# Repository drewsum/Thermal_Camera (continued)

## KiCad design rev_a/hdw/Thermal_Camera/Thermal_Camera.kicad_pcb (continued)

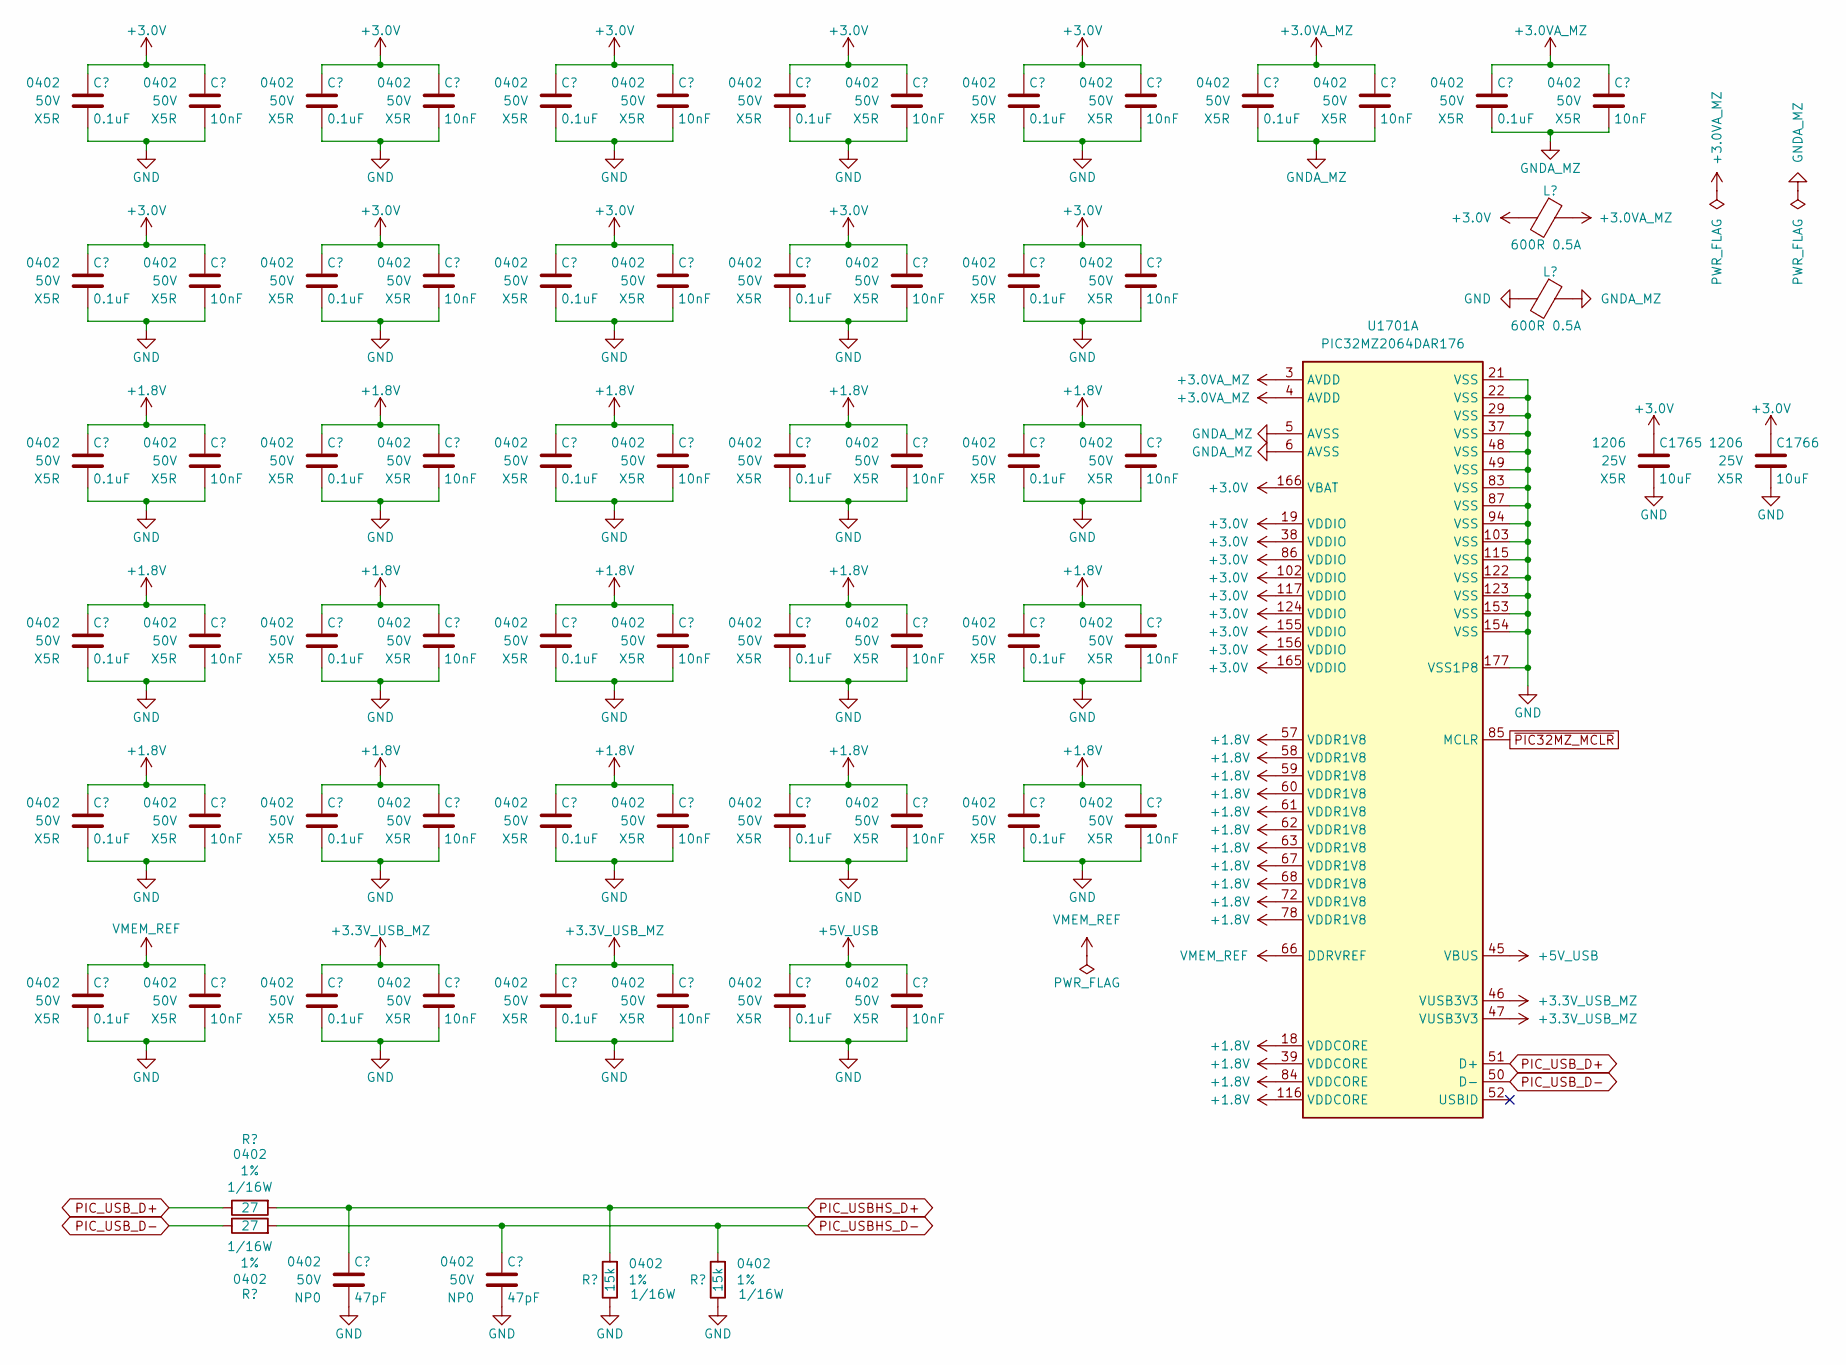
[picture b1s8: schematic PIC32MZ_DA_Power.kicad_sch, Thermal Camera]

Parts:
C1701, C1702, C1703, C1704, C1705, C1706, C1713, C1714, C1715, C1716, C1717, C1718, C1727, C1728, C1729, C1730, C1731, C1732, C1739, C1740, C1741, C1742, C1743, C1744, C1751, C1752, C1753, C1754, C1755, C1761, C1763: 0.1uF; C_0402; Voltage 50V; Digi-Key PN 490-10697-1-ND
C1707, C1708, C1709, C1710, C1711, C1712, C1720, C1721, C1722, C1723, C1724, C1725, C1733, C1734, C1735, C1736, C1737, C1738, C1745, C1746, C1747, C1748, C1749, C1750, C1756, C1757, C1758, C1759, C1760, C1762, C1764: 10nF; C_0402; Voltage 50V; Digi-Key PN 445-12201-1-ND
C1719, C1726: 47pF; C_0402; Voltage 50V; Digi-Key PN 490-5942-1-ND
C1765, C1766: 10uF; C_1206; Voltage 25V; Digi-Key PN 399-8153-1-ND
L1701, L1702: 600R 0.5A; L_0402
R1701, R1702: 27; R_0402; Tolerance 1%; Digi-Key PN RMCF0402FT27R0CT-ND
R1703, R1704: 15k; R_0402; Tolerance 1%; Digi-Key PN RMCF0402FT15K0CT-ND
U1701: PIC32MZ2064DAR176; LQFP-176_20x20mm_P0.4mm_7p9x7p9mm_EP; Digi-Key PN PIC32MZ2064DAR176-I/2J-ND

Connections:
+1.8V: C1703.1, C1704.1, C1705.1, C1709.1, C1710.1, C1711.1, C1715.1, C1716.1, C1717.1, C1722.1, C1723.1, C1724.1, C1729.1, C1730.1, C1731.1, C1735.1, C1736.1, C1737.1, C1741.1, C1742.1, C1743.1, C1747.1, C1748.1, C1749.1, C1753.1, C1754.1, C1755.1, C1758.1, C1759.1, C1760.1, U1701.18 (VDDCORE), U1701.39 (VDDCORE), U1701.57 (VDDR1V8), U1701.58 (VDDR1V8), U1701.59 (VDDR1V8), U1701.60 (VDDR1V8), U1701.61 (VDDR1V8), U1701.62 (VDDR1V8), U1701.63 (VDDR1V8), U1701.67 (VDDR1V8), U1701.68 (VDDR1V8), U1701.72 (VDDR1V8), U1701.78 (VDDR1V8), U1701.84 (VDDCORE), U1701.116 (VDDCORE); also elsewhere on the board
+3.0V: C1701.1, C1702.1, C1707.1, C1708.1, C1713.1, C1714.1, C1720.1, C1721.1, C1727.1, C1728.1, C1733.1, C1734.1, C1739.1, C1740.1, C1745.1, C1746.1, C1751.1, C1752.1, C1756.1, C1757.1, C1765.1, C1766.1, L1701.2, U1701.19 (VDDIO), U1701.38 (VDDIO), U1701.86 (VDDIO), U1701.102 (VDDIO), U1701.117 (VDDIO), U1701.124 (VDDIO), U1701.155 (VDDIO), U1701.156 (VDDIO), U1701.165 (VDDIO), U1701.166 (VBAT); also elsewhere on the board
+3.0VA_MZ: C1761.1, C1762.1, C1763.1, C1764.1, L1701.1, U1701.3 (AVDD), U1701.4 (AVDD)
+3.3V_USB_MZ: C1718.1, C1725.1, C1732.1, C1738.1, U1701.46 (VUSB3V3), U1701.47 (VUSB3V3)
+5V_USB: C1744.1, C1750.1, U1701.45 (VBUS); also elsewhere on the board
GND: C1701.2, C1702.2, C1703.2, C1704.2, C1705.2, C1706.2, C1707.2, C1708.2, C1709.2, C1710.2, C1711.2, C1712.2, C1713.2, C1714.2, C1715.2, C1716.2, C1717.2, C1718.2, C1719.2, C1720.2, C1721.2, C1722.2, C1723.2, C1724.2, C1725.2, C1726.2, C1727.2, C1728.2, C1729.2, C1730.2, C1731.2, C1732.2, C1733.2, C1734.2, C1735.2, C1736.2, C1737.2, C1738.2, C1739.2, C1740.2, C1741.2, C1742.2, C1743.2, C1744.2, C1745.2, C1746.2, C1747.2, C1748.2, C1749.2, C1750.2, C1751.2, C1752.2, C1753.2, C1754.2, C1755.2, C1756.2, C1757.2, C1758.2, C1759.2, C1760.2, C1765.2, C1766.2, L1702.2, R1703.2, R1704.2, U1701.21 (VSS), U1701.22 (VSS), U1701.29 (VSS), U1701.37 (VSS), U1701.48 (VSS), U1701.49 (VSS), U1701.83 (VSS), U1701.87 (VSS), U1701.94 (VSS), U1701.103 (VSS), U1701.115 (VSS), U1701.122 (VSS), U1701.123 (VSS), U1701.153 (VSS), U1701.154 (VSS), U1701.177 (VSS1P8); also elsewhere on the board
GNDA_MZ: C1761.2, C1762.2, C1763.2, C1764.2, L1702.1, U1701.5 (AVSS), U1701.6 (AVSS)
PIC_USBHS_D+: C1719.1, R1701.1, R1703.1; also elsewhere on the board
PIC_USBHS_D-: C1726.1, R1702.1, R1704.1; also elsewhere on the board
PIC_USB_D+: R1701.2, U1701.51 (D+)
PIC_USB_D-: R1702.2, U1701.50 (D-)
VMEM_REF: C1706.1, C1712.1, U1701.66 (DDRVREF)
~PIC32MZ_MCLR: U1701.85 (MCLR); also elsewhere on the board

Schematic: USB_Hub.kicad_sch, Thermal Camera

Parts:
C2501, C2502, C2503, C2504, C2506, C2507, C2509: 0.1uF; C_0402; Voltage 50V; Digi-Key PN 490-10697-1-ND
C2505, C2508: 10uF; C_0402; Voltage 10V; Digi-Key PN 490-GRM155R61A106ME11DCT-ND
L2501: 600R 0.5A; L_0402
R2501: 10; R_0402; Tolerance 1%; Digi-Key PN RMCF0402FT10R0CT-ND
R2502, R2503, R2504, R2505, R2506, R2507: 10k; R_0402; Tolerance 1%; Digi-Key PN RMCF0402FT10K0CT-ND
SW2501: RESET; SW_PUSH_6mm
U2501, U2503: 74LVC1G97; SOT-363_SC-70-6; Digi-Key PN 296-15582-1-ND
U2502: TPS3808G33; SOT-23-6; Digi-Key PN 296-17195-1-ND
U2504: TUSB2046BIRHBT; VQFN-32-1EP_5x5mm_P0.5mm_EP3.5x3.5mm; Digi-Key PN 296-27130-1-ND
X2501: ASE-48.000MHz; Oscillator_SMD_Abracon_ASE-4Pin_3.2x2.5mm; Digi-Key PN 535-ASE-48.000MHZ-L-C-TCT-ND

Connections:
+3.3V_USB: C2502.1, C2503.1, C2506.1, C2507.1, C2508.1, C2509.1, L2501.2, R2504.1, R2507.1, U2501.5 (VCC), U2502.5 (SENSE), U2502.6 (VDD), U2503.5 (VCC), U2504.3 (VCC), U2504.8 (BUSPWR), U2504.25 (VCC), U2504.26 (~EXTMEM), U2504.30 (XTAL1), U2504.31 (TSTMODE); also elsewhere on the board
BRIDGE_USB_D+: U2504.12 (DP1); also elsewhere on the board
BRIDGE_USB_D-: U2504.11 (DM1); also elsewhere on the board
GND: C2501.2, C2502.2, C2503.2, C2504.2, C2505.2, C2506.2, C2507.2, C2508.2, C2509.2, R2502.2, R2503.2, R2505.2, R2506.2, SW2501.1, U2501.2 (GND), U2501.3 (GND), U2501.6 (GND), U2502.2 (GND), U2503.2 (GND), U2503.3 (GND), U2503.6 (GND), U2504.6 (EEDATA/GANGED), U2504.7 (GND), U2504.28 (GND), U2504.33 (EP), X2501.2 (GND); also elsewhere on the board
HUB_48MHCLK: R2501.2, U2504.27 (TSTPLL/48MCLK)
HUB_CLK_EN: R2503.1, U2501.4, X2501.1 (EN)
HUB_SUSPND: R2505.1, U2503.4; also elsewhere on the board
unnamed: C2501.1, U2502.4 (CT)
unnamed: SW2501.2, U2502.3 (~MR)
unnamed: R2506.1, U2503.1, U2504.32 (SUSPND)
unnamed: R2507.2, U2504.10 (~OVRCUR1), U2504.14 (~OVRCUR2), U2504.18 (~OVRCUR3), U2504.22 (~OVRCUR4)
unnamed: R2501.1, R2502.1, X2501.3 (OUT)
unnamed: C2504.1, C2505.1, L2501.1, X2501.4 (Vdd)
PIC_USBHS_D+: U2504.16 (DP2); also elsewhere on the board
PIC_USBHS_D-: U2504.15 (DM2); also elsewhere on the board
POS3P3_USB_PGOOD: U2501.1; also elsewhere on the board
UFP_USB_D+: U2504.1 (DP0); also elsewhere on the board
UFP_USB_D-: U2504.2 (DM0); also elsewhere on the board
~HUB_RESET: R2504.2, U2502.1 (~RESET), U2504.4 (~RESET)

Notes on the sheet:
Generally, a reset with a pulse width between 100 μs and 1 ms is recommended after 3.3-V VCC reaches its 90%. Clock signal has to be active during the last 60 μs of the reset window.
Strap PLL for 48MHz clocking option See Figure 7 of D/S

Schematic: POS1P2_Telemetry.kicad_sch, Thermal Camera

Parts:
C1101, C1102, C1103: 0.1uF; C_0402; Voltage 50V; Digi-Key PN 490-10697-1-ND
DOC1101: 0x74
DOC1102: 0x1C
U1101: INA231A; Texas_DSBGA-12_1.65x1.39mm_Layout3x4_P0.4mm; Digi-Key PN 296-41263-1-ND
U1102: MCP9804; DFN-8-1EP_3x2mm_P0.5mm_EP1.3x1.5mm; Digi-Key PN MCP9804T-E/MCCT-ND

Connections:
+1.2V: U1101.D1 (BUS); also elsewhere on the board
+3.0V: C1102.1, C1103.1, U1101.B1 (VS), U1101.C3 (A1), U1102.5 (A2), U1102.8 (V_{DD}); also elsewhere on the board
GND: C1102.2, C1103.2, U1101.B3 (A0), U1101.C1 (GND), U1102.4 (GND), U1102.6 (A1), U1102.7 (A0), U1102.9 (EP/GND); also elsewhere on the board
I2C_SCL: U1101.A1 (SCL), U1102.2 (SCL); also elsewhere on the board
I2C_SDA: U1101.A2 (SDA), U1102.1 (SDA); also elsewhere on the board
POS1P2_SNS+: C1101.1, U1101.D3 (IN+)
POS1P2_SNS-: C1101.2, U1101.D2 (IN-)

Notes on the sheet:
Max Current = 3.1A RSHUNT = 0.02 Ohm CLSB = 9.46045E-05A CAL Register = 0x0A92

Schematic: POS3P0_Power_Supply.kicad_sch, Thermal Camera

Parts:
C401, C406: 0.1uF; C_0402; Voltage 50V; Digi-Key PN 490-10697-1-ND
C402, C404, C407, C408: 10uF; C_1206; Voltage 25V; Digi-Key PN 399-8153-1-ND
C403: 10uF; C_0402; Voltage 10V; Digi-Key PN 490-GRM155R61A106ME11DCT-ND
C405: 10nF; C_0402; Voltage 50V; Digi-Key PN 445-12201-1-ND
D401: BAT48JFILM; D_SOD-323; Digi-Key PN 497-5711-1-ND
L401: 2.2uH; L_Vishay_IHLP-2020; Tolerance 20%; Digi-Key PN 541-1236-1-ND
Q401: BSS214NW; SOT-323_SC-70; Digi-Key PN BSS214NWH6327XTSA1CT-ND
Q402: ZXMS6004FFTA; SOT-23; Digi-Key PN ZXMS6004FFCT-ND
R401, R405, R407: 10; R_0402; Tolerance 1%; Digi-Key PN RMCF0402FT10R0CT-ND
R402, R403, R404: 10k; R_0402; Tolerance 1%; Digi-Key PN RMCF0402FT10K0CT-ND
R406: 0.02; R_0612; Tolerance 1%; Digi-Key PN P16010CT-ND
R408: 3.16k; R_0402; Tolerance 1%; Digi-Key PN RMCF0402FT3K16CT-ND
R409: 1.15k; R_0402; Tolerance 1%; Digi-Key PN RMCF0402FT1K15CT-ND
TP401: TP; Test_Point
U401: 74LVC1G97; SOT-363_SC-70-6; Digi-Key PN 296-15582-1-ND
U402: TPS62130A; QFN-16-1EP_3x3mm_P0.5mm_EP1.75x1.75mm; Digi-Key PN 296-39446-1-ND

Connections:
+3.0V: C401.1, D401.2 (A), Q402.3 (D), R403.1, R406.2, R407.2, R408.1, TP401.1 (TP), U401.5 (VCC), U402.14 (VOS); also elsewhere on the board
GND: C401.2, C402.2, C403.2, C404.2, C405.2, C406.2, C407.2, C408.2, Q401.2 (S), Q402.2 (S), R402.2, R409.2, U401.1 (GND), U401.2 (GND), U402.6 (AGND), U402.7 (FSW), U402.8 (DEF), U402.15 (PGND), U402.16 (PGND), U402.17 (EP); also elsewhere on the board
unnamed: C407.1, C408.1, L401.2, R405.2, R406.1
unnamed: C403.1, D401.1 (K), R404.1
unnamed: L401.1, U402.1 (SW), U402.2 (SW), U402.3 (SW)
unnamed: Q401.3 (D), Q402.1 (G), R404.2
unnamed: R408.2, R409.1, U402.5 (FB)
unnamed: R403.2, U401.6, U402.4 (PG)
unnamed: C405.1, U402.9 (SS/TR)
POS3P0_PGOOD: R402.1, U401.4; also elsewhere on the board
POS3P0_RUN: Q401.1 (G), R401.2, U401.3, U402.13 (EN)
POS3P0_SNS+: R405.1; also elsewhere on the board
POS3P0_SNS-: R407.1; also elsewhere on the board
POS12_PGOOD: R401.1; also elsewhere on the board
VCOM: C402.1, C404.1, C406.1, U402.10 (AVIN), U402.11 (PVIN), U402.12 (PVIN); also elsewhere on the board

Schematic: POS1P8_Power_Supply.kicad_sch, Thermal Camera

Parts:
C601, C606: 0.1uF; C_0402; Voltage 50V; Digi-Key PN 490-10697-1-ND
C602, C604, C607, C608: 10uF; C_1206; Voltage 25V; Digi-Key PN 399-8153-1-ND
C603: 10uF; C_0402; Voltage 10V; Digi-Key PN 490-GRM155R61A106ME11DCT-ND
C605: 10nF; C_0402; Voltage 50V; Digi-Key PN 445-12201-1-ND
D601: BAT48JFILM; D_SOD-323; Digi-Key PN 497-5711-1-ND
L601: 2.2uH; L_Vishay_IHLP-2020; Tolerance 20%; Digi-Key PN 541-1236-1-ND
Q601: BSS214NW; SOT-323_SC-70; Digi-Key PN BSS214NWH6327XTSA1CT-ND
Q602: ZXMS6004FFTA; SOT-23; Digi-Key PN ZXMS6004FFCT-ND
R601, R605, R607: 10; R_0402; Tolerance 1%; Digi-Key PN RMCF0402FT10R0CT-ND
R602, R603, R604: 10k; R_0402; Tolerance 1%; Digi-Key PN RMCF0402FT10K0CT-ND
R606: 0.02; R_0612; Tolerance 1%; Digi-Key PN P16010CT-ND
R608: 1.87k; R_0402; Tolerance 1%; Digi-Key PN RMCF0402FT1K87CT-ND
R609: 1.5k; R_0402; Tolerance 1%; Digi-Key PN RMCF0402FT1K50CT-ND
TP601: TP; Test_Point
U601: 74LVC1G97; SOT-363_SC-70-6; Digi-Key PN 296-15582-1-ND
U602: TPS62130A; QFN-16-1EP_3x3mm_P0.5mm_EP1.75x1.75mm; Digi-Key PN 296-39446-1-ND

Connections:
+1.8V: Q602.3 (D), R606.2, R607.2, R608.1, TP601.1 (TP), U602.14 (VOS); also elsewhere on the board
+3.0V: C601.1, D601.2 (A), R603.1, U601.5 (VCC); also elsewhere on the board
GND: C601.2, C602.2, C603.2, C604.2, C605.2, C606.2, C607.2, C608.2, Q601.2 (S), Q602.2 (S), R602.2, R609.2, U601.1 (GND), U601.2 (GND), U602.6 (AGND), U602.7 (FSW), U602.8 (DEF), U602.15 (PGND), U602.16 (PGND), U602.17 (EP); also elsewhere on the board
unnamed: C607.1, C608.1, L601.2, R605.2, R606.1
unnamed: C603.1, D601.1 (K), R604.1
unnamed: L601.1, U602.1 (SW), U602.2 (SW), U602.3 (SW)
unnamed: Q601.3 (D), Q602.1 (G), R604.2
unnamed: R608.2, R609.1, U602.5 (FB)
unnamed: R603.2, U601.6, U602.4 (PG)
unnamed: C605.1, U602.9 (SS/TR)
POS1P8_PGOOD: R602.1, U601.4; also elsewhere on the board
POS1P8_RUN: Q601.1 (G), R601.2, U601.3, U602.13 (EN)
POS1P8_SNS+: R605.1; also elsewhere on the board
POS1P8_SNS-: R607.1; also elsewhere on the board
POS3P0_PGOOD: R601.1; also elsewhere on the board
VCOM: C602.1, C604.1, C606.1, U602.10 (AVIN), U602.11 (PVIN), U602.12 (PVIN); also elsewhere on the board

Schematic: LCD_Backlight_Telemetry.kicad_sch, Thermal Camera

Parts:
C1301, C1302, C1303: 0.1uF; C_0402; Voltage 50V; Digi-Key PN 490-10697-1-ND
DOC1301: 0x75
DOC1302: 0x1D
U1301: INA231A; Texas_DSBGA-12_1.65x1.39mm_Layout3x4_P0.4mm; Digi-Key PN 296-41263-1-ND
U1302: MCP9804; DFN-8-1EP_3x2mm_P0.5mm_EP1.3x1.5mm; Digi-Key PN MCP9804T-E/MCCT-ND

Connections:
+3.0V: C1302.1, C1303.1, U1301.B1 (VS), U1301.B3 (A0), U1301.C3 (A1), U1302.5 (A2), U1302.7 (A0), U1302.8 (V_{DD}); also elsewhere on the board
BACKLIGHT_ANODE: U1301.D1 (BUS); also elsewhere on the board
GND: C1302.2, C1303.2, U1301.C1 (GND), U1302.4 (GND), U1302.6 (A1), U1302.9 (EP/GND); also elsewhere on the board
I2C_SCL: U1301.A1 (SCL), U1302.2 (SCL); also elsewhere on the board
I2C_SDA: U1301.A2 (SDA), U1302.1 (SDA); also elsewhere on the board
VLED_SNS+: C1301.1, U1301.D3 (IN+); also elsewhere on the board
VLED_SNS-: C1301.2, U1301.D2 (IN-); also elsewhere on the board

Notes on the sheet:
Max Current = 3.1A RSHUNT = 0.02 Ohm CLSB = 9.46045E-05A CAL Register = 0x0A92

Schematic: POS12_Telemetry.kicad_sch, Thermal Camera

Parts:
C301, C302, C303: 0.1uF; C_0402; Voltage 50V; Digi-Key PN 490-10697-1-ND
DOC301: 0x70
DOC302: 0x18
U301: INA231A; Texas_DSBGA-12_1.65x1.39mm_Layout3x4_P0.4mm; Digi-Key PN 296-41263-1-ND
U302: MCP9804; DFN-8-1EP_3x2mm_P0.5mm_EP1.3x1.5mm; Digi-Key PN MCP9804T-E/MCCT-ND

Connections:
+3.0V: C302.1, C303.1, U301.B1 (VS), U302.8 (V_{DD}); also elsewhere on the board
+12V: U301.D1 (BUS); also elsewhere on the board
GND: C302.2, C303.2, U301.B3 (A0), U301.C1 (GND), U301.C3 (A1), U302.4 (GND), U302.5 (A2), U302.6 (A1), U302.7 (A0), U302.9 (EP/GND); also elsewhere on the board
I2C_SCL: U301.A1 (SCL), U302.2 (SCL); also elsewhere on the board
I2C_SDA: U301.A2 (SDA), U302.1 (SDA); also elsewhere on the board
POS12_SNS+: C301.1, U301.D3 (IN+); also elsewhere on the board
POS12_SNS-: C301.2, U301.D2 (IN-); also elsewhere on the board

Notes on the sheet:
Max Current = 3.1A RSHUNT = 0.02 Ohm CLSB = 9.46045E-05A CAL Register = 0x0A92

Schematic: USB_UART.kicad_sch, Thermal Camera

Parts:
C2201, C2202, C2203, C2204, C2207, C2210: 0.1uF; C_0402; Voltage 50V; Digi-Key PN 490-10697-1-ND
C2205, C2206, C2211: 10uF; C_0402; Voltage 10V; Digi-Key PN 490-GRM155R61A106ME11DCT-ND
C2208, C2209: 47pF; C_0402; Voltage 50V; Digi-Key PN 490-5942-1-ND
D2201: Yellow; LED_0402; Digi-Key PN VLMY1500-GS08CT-ND
DOC2201: COM_Port_Settings
R2201: 1k; R_0402; Tolerance 1%; Digi-Key PN RMCF0402FT1K00CT-ND
R2202: 10k; R_0402; Tolerance 1%; Digi-Key PN RMCF0402FT10K0CT-ND
R2203, R2204: 27; R_0402; Tolerance 1%; Digi-Key PN RMCF0402FT27R0CT-ND
R2205, R2206: 15k; R_0402; Tolerance 1%; Digi-Key PN RMCF0402FT15K0CT-ND
U2201: FT234XD; DFN-12-1EP_3x3mm_Pitch0.45mm; Digi-Key PN 768-1178-1-ND
U2202: 74LVC1G97; SOT-363_SC-70-6; Digi-Key PN 296-15582-1-ND
U2203: FXMA108; WQFN-20-1EP_2.5x4.5mm_P0.5mm_EP1x2.9mm; Digi-Key PN FXMA108BQX

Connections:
+3.0V: C2202.1, C2204.1, C2205.1, R2202.1, U2202.1 (VCC), U2202.5 (VCC), U2203.1 (VCCA); also elsewhere on the board
+3.3V_USB: C2201.1, C2210.1, C2211.1, U2201.9 (VCCIO), U2203.20 (VCCB); also elsewhere on the board
+5V_USB: C2203.1, C2206.1, R2201.1, U2201.4 (VCC); also elsewhere on the board
/USB UART/BRIDGE_USB+: R2203.2, U2201.12 (USBDP)
/USB UART/BRIDGE_USB-: R2204.2, U2201.1 (USBDM)
BRIDGE_USB_D+: C2208.1, R2203.1, R2205.1; also elsewhere on the board
BRIDGE_USB_D-: C2209.1, R2204.1, R2206.1; also elsewhere on the board
GND: C2201.2, C2202.2, C2203.2, C2204.2, C2205.2, C2206.2, C2207.2, C2208.2, C2209.2, C2210.2, C2211.2, R2205.2, R2206.2, U2201.5 (GND), U2201.13 (GND), U2202.2 (GND), U2202.3 (GND), U2203.10 (GND); also elsewhere on the board
unnamed: D2201.2 (A), R2201.2
unnamed: C2207.1, U2201.3 (3V3OUT)
unnamed: R2202.2, U2202.4, U2203.11 (~OE)
POS3P0_PGOOD: U2202.6; also elsewhere on the board
POS3P3_USB_PGOOD: U2201.2 (~RESET); also elsewhere on the board
USB_UART_RX: U2203.2 (A0); also elsewhere on the board
USB_UART_RX_BUF: U2201.7 (TXD), U2203.19 (B0)
USB_UART_TX: U2203.3 (A1); also elsewhere on the board
USB_UART_TX_BUF: U2201.10 (RXD), U2203.18 (B1)
~USB_ACTIVE: D2201.1 (K), U2201.6 (CBUS0)
~USB_UART_CTS_BUF: U2201.11 (~CTS), U2203.16 (B3)
~USB_UART_CTS: U2203.5 (A3); also elsewhere on the board
~USB_UART_RTS_BUF: U2201.8 (~RTS), U2203.17 (B2)
~USB_UART_RTS: U2203.4 (A2); also elsewhere on the board

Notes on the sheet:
FXMA108 recommends no pull resistors

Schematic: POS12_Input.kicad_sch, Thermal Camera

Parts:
C201: 10nF; C_0402; Voltage 50V; Digi-Key PN 445-12201-1-ND
C202: 0.1uF; C_0402; Voltage 50V; Digi-Key PN 490-10697-1-ND
C203: 100uF; CP_EIA-7343-43_Kemet-X; Voltage 16V; Tolerance 10%; Digi-Key PN 718-1102-1-ND
D201: 24V; D_SMA; Digi-Key PN SMAJ24CALFCT-ND; not fitted
J201: +12V IN; BARREL_JACK
N201: +12V 1A Power Supply; Digi-Key PN 993-1335-ND
R201: 51.1k; R_0402; Tolerance 1%; Digi-Key PN RMCF0402FT51K1CT-ND
R202, R209: 1.15k; R_0402; Tolerance 1%; Digi-Key PN RMCF0402FT1K15CT-ND
R203, R208: 5.11k; R_0402; Tolerance 1%; Digi-Key PN RMCF0402FT5K11CT-ND
R204, R206, R211: 10k; R_0402; Tolerance 1%; Digi-Key PN RMCF0402FT10K0CT-ND
R205, R210: 10; R_0402; Tolerance 1%; Digi-Key PN RMCF0402FT10R0CT-ND
R207: 0.02; R_0612; Tolerance 1%; Digi-Key PN P16010CT-ND
TP201: TP; PinHeader_1x01_P2.54mm_Horizontal
TP202, TP203: TP; Test_Point
U201: TPS26600RHFT; QFN-24-1EP_4x5mm_Pitch0.5mm; Digi-Key PN 296-45478-1-ND

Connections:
+12V: C203.1, R207.2, R208.1, R210.2, TP203.1 (TP); also elsewhere on the board
+12Vin: C202.1, D201.1 (A1), J201.1, R201.1, R204.1, TP202.1 (TP), U201.8 (IN), U201.9 (IN)
GND: C202.2, C203.2, D201.2 (A2), J201.2, J201.3, R209.2, TP201.1 (TP), U201.17 (GND); also elsewhere on the board
unnamed: R205.2, R207.1, U201.23 (OUT), U201.24 (OUT)
unnamed: R206.1, U201.19 (ILIM)
unnamed: R211.1, U201.18 (IMON)
unnamed: R202.2, R203.1, U201.12 (OVP)
unnamed: C201.2, R203.2, R206.2, R211.2, U201.15 (RTN), U201.25 (RTN_PAD)
unnamed: R201.2, R202.1, U201.10 (UVLO)
unnamed: C201.1, U201.20 (dVdT)
unnamed: R204.2, U201.14 (~SHDN)
POS12_PGOOD: R208.2, R209.1, U201.22 (~FLT); also elsewhere on the board
POS12_SNS+: R205.1; also elsewhere on the board
POS12_SNS-: R210.1; also elsewhere on the board

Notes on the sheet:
UVLO threshold set to 10.8V OVLO threshold set to 13.2V MODE set to Circuit Breaker with Auto-Retry Output Current Limit set to 1.2A
+3.0V logic level at +13.2Vin

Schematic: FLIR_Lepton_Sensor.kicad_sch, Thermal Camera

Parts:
C2401, C2403, C2404, C2405: 0.1uF; C_0402; Voltage 50V; Digi-Key PN 490-10697-1-ND
C2402: 10uF; C_0402; Voltage 10V; Digi-Key PN 490-GRM155R61A106ME11DCT-ND
DOC2401: 0x2A
L2401: 600R 0.5A; L_0402
N2401: Lepton3.5 Sensor; Digi-Key PN 500-0771-01-ND
R2401, R2402, R2403, R2404, R2405, R2406, R2407, R2408, R2409: 10k; R_0402; Tolerance 1%; Digi-Key PN RMCF0402FT10K0CT-ND
R2410, R2411, R2412, R2413, R2414, R2415: 10; R_0402; Tolerance 1%; Digi-Key PN RMCF0402FT10R0CT-ND
U2401: FLIR_Lepton3p5_Socket; MOLEX_105028-1001; Digi-Key PN 1050281001
X2401: ECS-2520MV-250-CN; Oscillator_SMD_ECS_2520MV-xxx-xx-4Pin_2.5x2.0mm; Digi-Key PN XC2752CT-ND

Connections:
+1.2V: C2403.1, U2401.7 (VDDC); also elsewhere on the board
+2.8V: C2405.1, U2401.19 (VDD); also elsewhere on the board
+3.0V: C2404.1, L2401.2, R2402.1, R2403.1, R2405.1, R2407.1, U2401.16 (VDDIO); also elsewhere on the board
FLIR_CLK: R2415.2, U2401.26 (MASTER_CLK)
FLIR_CLK_EN: R2401.1, X2401.1 (Tri-State); also elsewhere on the board
FLIR_VOSPI_CLK: R2403.2, R2412.2; also elsewhere on the board
FLIR_VOSPI_MISO: R2405.2, R2411.2; also elsewhere on the board
FLIR_VOSPI_MOSI: R2407.2, R2410.2; also elsewhere on the board
FLIR_VOSPI_VSYNC: R2404.1, R2414.2; also elsewhere on the board
GND: C2401.2, C2402.2, C2403.2, C2404.2, C2405.2, R2401.2, R2404.2, R2406.2, R2408.2, R2409.2, U2401.1 (G1), U2401.6 (G6), U2401.8 (G8), U2401.9 (G9), U2401.10 (G10), U2401.15 (G15), U2401.18 (G18), U2401.25 (G25), U2401.27 (G27), U2401.30 (G30), U2401.P1 (SHEILD), U2401.P2 (G34), U2401.P3 (G35), U2401.P4 (G36), U2401.P5 (G37), U2401.P6 (G38), U2401.P7 (G39), U2401.P8 (G40), U2401.P9 (G41), U2401.P10 (G42), U2401.P11 (G43), U2401.P12 (G44), U2401.P13 (G45), U2401.P14 (G46), U2401.P15 (G47), U2401.P16 (G48), U2401.P17 (G49), U2401.P18 (G50), U2401.P19 (G51), U2401.P20 (G52), U2401.P21 (G53), U2401.P22 (G54), U2401.P23 (G55), U2401.P24 (G56), U2401.P25 (G57), U2401.P26 (G58), U2401.P27 (G59), U2401.P28 (G60), U2401.P29 (G61), U2401.P30 (G62), U2401.P31 (G63), U2401.P32 (G64), U2401.P33 (G65), U2401.P34 (G66), U2401.P35 (G67), U2401.P36 (G68), X2401.2 (GND); also elsewhere on the board
I2C_SCL: U2401.21 (SCL); also elsewhere on the board
I2C_SDA: U2401.22 (SDA); also elsewhere on the board
unnamed: R2414.1, U2401.2 (GPIO3)
unnamed: R2412.1, U2401.13 (SPI_CLK)
unnamed: R2411.1, U2401.12 (SPI_MISO)
unnamed: R2410.1, U2401.11 (SPI_MOSI)
unnamed: R2413.1, U2401.14 (~SPI_CS)
unnamed: R2409.1, R2415.1, X2401.3 (OUT)
unnamed: C2401.1, C2402.1, L2401.1, X2401.4 (VDD)
~FLIR_PWR_DWN: R2406.1, U2401.23 (~PWR_DWN); also elsewhere on the board
~FLIR_RESET: R2408.1, U2401.24 (~RESET); also elsewhere on the board
~FLIR_VOSPI_CS: R2402.2, R2413.2; also elsewhere on the board

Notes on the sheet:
Power Supply Considerations: VDDC: 1.20V (1.14V min, 1.26V max), 50mVpp max ripple, 110mA max draw VDD: 2.80V (2.72V min, 2.88V max), 30mVpp max ripple, 16mA max draw VDDIO: 2.8V min, 3.1V max, 50mVpp max ripple, 310mA max draw
See FLIR document #110-0144-04 for I2C register map

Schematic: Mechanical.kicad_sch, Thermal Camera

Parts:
H2001, H2002, H2003, H2004: MountingHole; MountingHole_3mm

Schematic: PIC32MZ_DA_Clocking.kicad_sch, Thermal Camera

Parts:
C1601, C1602, C1603: 0.1uF; C_0402; Voltage 50V; Digi-Key PN 490-10697-1-ND
C1604, C1605: 10uF; C_0402; Voltage 10V; Digi-Key PN 490-GRM155R61A106ME11DCT-ND
L1601, L1602: 600R 0.5A; L_0402
R1601, R1602, R1603, R1604: 10k; R_0402; Tolerance 1%; Digi-Key PN RMCF0402FT10K0CT-ND
R1605, R1606: 10; R_0402; Tolerance 1%; Digi-Key PN RMCF0402FT10R0CT-ND
TP1601: TP; Test_Point
U1601: 74LVC1G97; SOT-363_SC-70-6; Digi-Key PN 296-15582-1-ND
X1601: ECS-2520MV-240-BN; Oscillator_SMD_ECS_2520MV-xxx-xx-4Pin_2.5x2.0mm; Digi-Key PN XC2750CT-ND
X1602: ECS-327KE; Digi-Key PN XC1751CT-ND

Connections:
+3.0V: C1601.1, L1601.2, L1602.2, U1601.5 (VCC); also elsewhere on the board
GND: C1601.2, C1602.2, C1603.2, C1604.2, C1605.2, R1601.2, R1602.2, R1603.2, R1604.2, U1601.2 (GND), U1601.3 (GND), U1601.6 (GND), X1601.2 (GND), X1602.2 (GND); also elsewhere on the board
unnamed: R1603.1, R1605.1, X1601.3 (OUT)
unnamed: C1602.1, C1604.1, L1601.1, X1601.4 (VDD)
unnamed: R1604.1, R1606.1, X1602.3 (OUT)
unnamed: C1603.1, C1605.1, L1602.1, X1602.4 (Vdd)
PIC32MZ_CLK_EN: R1602.1, U1601.4, X1601.1 (Tri-State), X1602.1 (EN)
PIC32MZ_POSC_EC: R1605.2; also elsewhere on the board
PIC32MZ_REFCLK1: R1601.1, TP1601.1 (TP); also elsewhere on the board
PIC32MZ_SOSC_EC: R1606.2; also elsewhere on the board
POS3P0_PGOOD: U1601.1; also elsewhere on the board

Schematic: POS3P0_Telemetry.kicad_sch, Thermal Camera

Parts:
C501, C502, C503: 0.1uF; C_0402; Voltage 50V; Digi-Key PN 490-10697-1-ND
DOC501: 0x71
DOC502: 0x19
U501: INA231A; Texas_DSBGA-12_1.65x1.39mm_Layout3x4_P0.4mm; Digi-Key PN 296-41263-1-ND
U502: MCP9804; DFN-8-1EP_3x2mm_P0.5mm_EP1.3x1.5mm; Digi-Key PN MCP9804T-E/MCCT-ND

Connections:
+3.0V: C502.1, C503.1, U501.B1 (VS), U501.B3 (A0), U501.D1 (BUS), U502.7 (A0), U502.8 (V_{DD}); also elsewhere on the board
GND: C502.2, C503.2, U501.C1 (GND), U501.C3 (A1), U502.4 (GND), U502.5 (A2), U502.6 (A1), U502.9 (EP/GND); also elsewhere on the board
I2C_SCL: U501.A1 (SCL), U502.2 (SCL); also elsewhere on the board
I2C_SDA: U501.A2 (SDA), U502.1 (SDA); also elsewhere on the board
POS3P0_SNS+: C501.1, U501.D3 (IN+); also elsewhere on the board
POS3P0_SNS-: C501.2, U501.D2 (IN-); also elsewhere on the board

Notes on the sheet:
Max Current = 3.1A RSHUNT = 0.02 Ohm CLSB = 9.46045E-05A CAL Register = 0x0A92

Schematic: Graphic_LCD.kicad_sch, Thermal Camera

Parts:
C2101, C2103: 0.1uF; C_0402; Voltage 50V; Digi-Key PN 490-10697-1-ND
C2102, C2104: 10uF; C_1206; Voltage 25V; Digi-Key PN 399-8153-1-ND
DOC2101: 0x28
J2101: LCD Pixel Data; GCT_FFC2B35-54-G_REVA2; Digi-Key PN 26-FH12-40S-0.5SH(55)CT-ND
J2102: LCD CTP Data
N2101: LCD Module; GLT035320240IS1-CTP; Digi-Key PN GLT035320240IS1-CTP
R2101, R2102, R2103, R2104: 10k; R_0402; Tolerance 1%; Digi-Key PN RMCF0402FT10K0CT-ND
RN2101, RN2102, RN2103, RN2104: 10k; R_Array_Convex_8x0602; Tolerance 1%; Digi-Key PN Y1103CT-ND

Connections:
+3.0V: C2101.1, C2102.1, C2103.1, C2104.1, J2101.41, J2101.42, J2102.2; also elsewhere on the board
BACKLIGHT_ANODE: J2101.3, J2101.4; also elsewhere on the board
BACKLIGHT_CATHODE: J2101.1, J2101.2; also elsewhere on the board
GLCD_B0: J2101.12, RN2101.16 (R1.2); also elsewhere on the board
GLCD_B1: J2101.13, RN2101.15 (R2.2); also elsewhere on the board
GLCD_B2: J2101.14, RN2101.14 (R3.2); also elsewhere on the board
GLCD_B3: J2101.15, RN2101.13 (R4.2); also elsewhere on the board
GLCD_B4: J2101.16, RN2101.12 (R5.2); also elsewhere on the board
GLCD_B5: J2101.17, RN2101.11 (R6.2); also elsewhere on the board
GLCD_B6: J2101.18, RN2101.10 (R7.2); also elsewhere on the board
GLCD_B7: J2101.19, RN2101.9 (R8.2); also elsewhere on the board
GLCD_G0: J2101.20, RN2102.16 (R1.2); also elsewhere on the board
GLCD_G1: J2101.21, RN2102.15 (R2.2); also elsewhere on the board
GLCD_G2: J2101.22, RN2102.14 (R3.2); also elsewhere on the board
GLCD_G3: J2101.23, RN2102.13 (R4.2); also elsewhere on the board
GLCD_G4: J2101.24, RN2102.12 (R5.2); also elsewhere on the board
GLCD_G5: J2101.25, RN2102.11 (R6.2); also elsewhere on the board
GLCD_G6: J2101.26, RN2102.10 (R7.2); also elsewhere on the board
GLCD_G7: J2101.27, RN2102.9 (R8.2); also elsewhere on the board
GLCD_GCLK: J2101.38, RN2104.14 (R3.2); also elsewhere on the board
GLCD_GEN: J2101.52, R2104.1; also elsewhere on the board
GLCD_HSYNC: J2101.36, RN2104.16 (R1.2); also elsewhere on the board
GLCD_R0: J2101.28, RN2103.16 (R1.2); also elsewhere on the board
GLCD_R1: J2101.29, RN2103.15 (R2.2); also elsewhere on the board
GLCD_R2: J2101.30, RN2103.14 (R3.2); also elsewhere on the board
GLCD_R3: J2101.31, RN2103.13 (R4.2); also elsewhere on the board
GLCD_R4: J2101.32, RN2103.12 (R5.2); also elsewhere on the board
GLCD_R5: J2101.33, RN2103.11 (R6.2); also elsewhere on the board
GLCD_R6: J2101.34, RN2103.10 (R7.2); also elsewhere on the board
GLCD_R7: J2101.35, RN2103.9 (R8.2); also elsewhere on the board
GLCD_VSYNC: J2101.37, RN2104.15 (R2.2); also elsewhere on the board
GND: C2101.2, C2102.2, C2103.2, C2104.2, J2101.53, J2101.54, J2101.S1, J2101.S2, J2102.1, R2101.2, R2102.2, R2103.2, R2104.2, RN2101.1 (R1.1), RN2101.2 (R2.1), RN2101.3 (R3.1), RN2101.4 (R4.1), RN2101.5 (R5.1), RN2101.6 (R6.1), RN2101.7 (R7.1), RN2101.8 (R8.1), RN2102.1 (R1.1), RN2102.2 (R2.1), RN2102.3 (R3.1), RN2102.4 (R4.1), RN2102.5 (R5.1), RN2102.6 (R6.1), RN2102.7 (R7.1), RN2102.8 (R8.1), RN2103.1 (R1.1), RN2103.2 (R2.1), RN2103.3 (R3.1), RN2103.4 (R4.1), RN2103.5 (R5.1), RN2103.6 (R6.1), RN2103.7 (R7.1), RN2103.8 (R8.1), RN2104.1 (R1.1), RN2104.2 (R2.1), RN2104.3 (R3.1), RN2104.4 (R4.1), RN2104.5 (R5.1), RN2104.6 (R6.1), RN2104.7 (R7.1), RN2104.8 (R8.1); also elsewhere on the board
LCD _CTP_RESET: J2102.6, R2102.1; also elsewhere on the board
LCD_CTP_INT: J2102.3, R2101.1; also elsewhere on the board
LCD_ENABLE: J2101.8, R2103.1; also elsewhere on the board

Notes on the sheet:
CTP connector TBD
GLT035320240IS1-CTP
CTP Controller: GT911(COF)

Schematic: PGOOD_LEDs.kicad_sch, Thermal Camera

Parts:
C2701, C2702, C2703, C2704, C2705, C2706, C2707: 0.1uF; C_0402; Voltage 50V; Digi-Key PN 490-10697-1-ND
D2701, D2702, D2704, D2705, D2706, D2707: Green; LED_0402; Digi-Key PN 1497-1219-1-ND
D2703: Red; LED_0402; Digi-Key PN VLMS1500-GS08CT-ND
R2701: 10k; R_0402; Tolerance 1%; Digi-Key PN RMCF0402FT10K0CT-ND
R2702, R2703, R2704, R2705, R2706, R2707, R2708: 1k; R_0402; Tolerance 1%; Digi-Key PN RMCF0402FT1K00CT-ND
U2701, U2702, U2703, U2704, U2705, U2706, U2707: 74LVC1G97; SOT-363_SC-70-6; Digi-Key PN 296-15582-1-ND

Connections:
+3.0V: C2701.1, C2702.1, C2703.1, C2704.1, C2705.1, C2706.1, R2702.1, R2703.1, R2704.1, R2705.1, R2706.1, R2707.1, U2701.1 (VCC), U2701.5 (VCC), U2702.1 (VCC), U2702.5 (VCC), U2703.1 (VCC), U2703.5 (VCC), U2704.1 (VCC), U2704.5 (VCC), U2705.1 (VCC), U2705.5 (VCC), U2706.1 (VCC), U2706.5 (VCC); also elsewhere on the board
+3.3V_USB: C2707.1, R2708.1, U2707.1 (VCC), U2707.5 (VCC); also elsewhere on the board
BATT_LOWBAT: U2703.6; also elsewhere on the board
GND: C2701.2, C2702.2, C2703.2, C2704.2, C2705.2, C2706.2, C2707.2, R2701.2, U2701.2 (GND), U2702.2 (GND), U2703.2 (GND), U2704.2 (GND), U2705.2 (GND), U2706.2 (GND), U2707.2 (GND), U2707.3 (GND); also elsewhere on the board
unnamed: D2701.2 (A), R2702.2
unnamed: D2701.1 (K), U2701.4
unnamed: D2702.2 (A), R2703.2
unnamed: D2702.1 (K), U2702.4
unnamed: D2703.2 (A), R2704.2
unnamed: D2703.1 (K), U2703.4
unnamed: D2704.2 (A), R2705.2
unnamed: D2704.1 (K), U2704.4
unnamed: D2705.2 (A), R2706.2
unnamed: D2705.1 (K), U2705.4
unnamed: D2706.2 (A), R2707.2
unnamed: D2706.1 (K), U2706.4
unnamed: D2707.2 (A), R2708.2
unnamed: D2707.1 (K), U2707.4
PGOOD_LED_SHDN: R2701.1, U2701.3, U2702.3, U2703.3, U2704.3, U2705.3, U2706.3; also elsewhere on the board
POS1P2_PGOOD: U2705.6; also elsewhere on the board
POS1P8_PGOOD: U2702.6; also elsewhere on the board
POS2P8_PGOOD: U2706.6; also elsewhere on the board
POS3P0_PGOOD: U2704.6; also elsewhere on the board
POS3P3_USB_PGOOD: U2707.6; also elsewhere on the board
POS12_PGOOD: U2701.6; also elsewhere on the board

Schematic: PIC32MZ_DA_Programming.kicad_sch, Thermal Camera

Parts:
C1501, C1502: 0.1uF; C_0402; Voltage 50V; Digi-Key PN 490-10697-1-ND
D1501: PESD3V3L5UY; SOT-363_SC-70-6; Digi-Key PN 1727-3828-1-ND
J1501: PICKIT4; PICKIT4_Header
J1502: MRST; PinHeader_1x02_P2.54mm_Vertical
L1501, L1502: 600R 0.5A; L_0402
Q1501: BSS214NW; SOT-323_SC-70; Digi-Key PN BSS214NWH6327XTSA1CT-ND
R1501, R1503: 10; R_0402; Tolerance 1%; Digi-Key PN RMCF0402FT10R0CT-ND
R1502, R1504: 10k; R_0402; Tolerance 1%; Digi-Key PN RMCF0402FT10K0CT-ND
R1505: 1k; R_0402; Tolerance 1%; Digi-Key PN RMCF0402FT1K00CT-ND
SW1501: MRST; SW_PUSH_6mm

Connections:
+3.0V: C1502.1, D1501.1 (K1), J1501.2, J1502.1, R1504.1, SW1501.1; also elsewhere on the board
GND: C1501.2, C1502.2, D1501.2 (A), L1502.2, Q1501.2 (S), R1502.2; also elsewhere on the board
unnamed: C1501.1, R1503.2, R1504.2, R1505.2
unnamed: D1501.3 (K2), J1501.1, L1501.2
unnamed: J1501.3, L1502.1
unnamed: J1502.2, R1501.1, SW1501.2
unnamed: Q1501.3 (D), R1503.1
unnamed: Q1501.1 (G), R1501.2, R1502.1
PIC32MZ_ICSPCLK: D1501.5 (K4), J1501.5; also elsewhere on the board
PIC32MZ_ICSPDAT: D1501.6 (K5), J1501.4; also elsewhere on the board
~PIC32MZ_MCLR: L1501.1, R1505.1; also elsewhere on the board

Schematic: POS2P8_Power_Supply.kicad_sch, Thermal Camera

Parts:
C801, C802, C804, C805: 10uF; C_0402; Voltage 10V; Digi-Key PN 490-GRM155R61A106ME11DCT-ND
C803: 0.1uF; C_0402; Voltage 50V; Digi-Key PN 490-10697-1-ND
R801, R802: 10k; R_0402; Tolerance 1%; Digi-Key PN RMCF0402FT10K0CT-ND
R803, R805: 10; R_0402; Tolerance 1%; Digi-Key PN RMCF0402FT10R0CT-ND
R804: 0.02; R_0612; Tolerance 1%; Digi-Key PN P16010CT-ND
R806: 2.87k; R_0402; Tolerance 1%; Digi-Key PN RMCF0402FT2K87CT-ND
R807: 1.15k; R_0402; Tolerance 1%; Digi-Key PN RMCF0402FT1K15CT-ND
TP801: TP; Test_Point
U801: TPS7A92; Texas_S-PDSO-N10_EP1.2x2mm; Digi-Key PN TPS7A9201DSKR

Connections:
+2.8V: C804.1, C805.1, R806.1, TP801.1 (TP), U801.1 (OUT), U801.2 (OUT); also elsewhere on the board
+3.0V: C801.1, R801.1, R803.2, R804.1; also elsewhere on the board
GND: C801.2, C802.2, C803.2, C804.2, C805.2, R802.2, R807.2, U801.4 (GND), U801.6 (SS_CTRL), U801.11 (GND); also elsewhere on the board
unnamed: C802.1, R804.2, R805.2, U801.9 (IN), U801.10 (IN)
unnamed: R806.2, R807.1, U801.3 (FB)
unnamed: C803.1, U801.8 (NR/SS)
POS2P8_PGOOD: R801.2, U801.5 (PG); also elsewhere on the board
POS2P8_RUN: R802.1, U801.7 (EN); also elsewhere on the board
POS2P8_SNS+: R803.1; also elsewhere on the board
POS2P8_SNS-: R805.1; also elsewhere on the board

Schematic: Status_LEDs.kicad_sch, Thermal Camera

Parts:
C2801, C2802, C2803, C2804: 0.1uF; C_0402; Voltage 50V; Digi-Key PN 490-10697-1-ND
D2801: Green; LED_0402; Digi-Key PN 1497-1219-1-ND
D2802, D2803, D2804: Red; LED_0402; Digi-Key PN VLMS1500-GS08CT-ND
R2801, R2802, R2805, R2806: 10k; R_0402; Tolerance 1%; Digi-Key PN RMCF0402FT10K0CT-ND
R2803, R2804, R2807, R2808: 1k; R_0402; Tolerance 1%; Digi-Key PN RMCF0402FT1K00CT-ND
U2801, U2802, U2803, U2804: 74LVC1G97; SOT-363_SC-70-6; Digi-Key PN 296-15582-1-ND

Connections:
+3.0V: C2801.1, C2802.1, C2803.1, C2804.1, R2803.1, R2804.1, R2805.1, R2807.1, R2808.1, U2801.1 (VCC), U2801.5 (VCC), U2802.1 (VCC), U2802.5 (VCC), U2803.1 (VCC), U2803.5 (VCC), U2804.1 (VCC), U2804.5 (VCC); also elsewhere on the board
CPU_Trap_LED: R2806.1, U2804.6; also elsewhere on the board
Error_LED: R2802.1, U2802.6; also elsewhere on the board
GND: C2801.2, C2802.2, C2803.2, C2804.2, R2801.2, R2802.2, R2806.2, U2801.2 (GND), U2801.3 (GND), U2802.2 (GND), U2802.3 (GND), U2803.2 (GND), U2803.3 (GND), U2804.2 (GND), U2804.3 (GND); also elsewhere on the board
Heartbeat_LED: R2801.1, U2801.6; also elsewhere on the board
unnamed: D2801.2 (A), R2803.2
unnamed: D2801.1 (K), U2801.4
unnamed: D2802.2 (A), R2804.2
unnamed: D2802.1 (K), U2802.4
unnamed: D2803.2 (A), R2807.2
unnamed: D2803.1 (K), U2803.4
unnamed: D2804.2 (A), R2808.2
unnamed: D2804.1 (K), U2804.4
Reset_LED: R2805.2, U2803.6; also elsewhere on the board

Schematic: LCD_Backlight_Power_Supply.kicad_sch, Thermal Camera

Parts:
C1201, C1203, C1204: 10uF; C_1206; Voltage 25V; Digi-Key PN 399-8153-1-ND
C1202: 1uF; C_0402; Voltage 10V; Digi-Key PN 311-1439-1-ND
D1201: PMEG6010CEJ; D_SOD-323F; Digi-Key PN 1727-3882-1-ND
L1201: 22uH; L_Vishay_IHLP-2020; Tolerance 20%; Digi-Key PN 541-1243-1-ND
R1201: 10k; R_0402; Tolerance 1%; Digi-Key PN RMCF0402FT10K0CT-ND
R1202, R1203, R1204, R1206: 10; R_0402; Tolerance 1%; Digi-Key PN RMCF0402FT10R0CT-ND
R1205: 0.02; R_0612; Tolerance 1%; Digi-Key PN P16010CT-ND
U1201: DIO5661CD6; DFN-6-1EP_2x2mm_P0.65mm_EP1x1.6mm

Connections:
BACKLIGHT_ANODE: R1205.2, R1206.2; also elsewhere on the board
BACKLIGHT_CATHODE: R1202.1, R1203.1, U1201.1 (FB); also elsewhere on the board
BACKLIGHT_PWM: R1201.2, U1201.5 (EN); also elsewhere on the board
GND: C1201.2, C1202.2, C1204.2, R1201.1, R1202.2, R1203.2, U1201.3 (GND), U1201.7 (GND); also elsewhere on the board
unnamed: C1203.2, C1204.1
unnamed: D1201.2 (A), L1201.2, U1201.4 (LX)
unnamed: C1203.1, D1201.1 (K), R1204.2, R1205.1
VCOM: C1201.1, C1202.1, L1201.1, U1201.6 (VIN); also elsewhere on the board
VLED_SNS+: R1204.1; also elsewhere on the board
VLED_SNS-: R1206.1; also elsewhere on the board

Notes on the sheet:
If = 40mA
